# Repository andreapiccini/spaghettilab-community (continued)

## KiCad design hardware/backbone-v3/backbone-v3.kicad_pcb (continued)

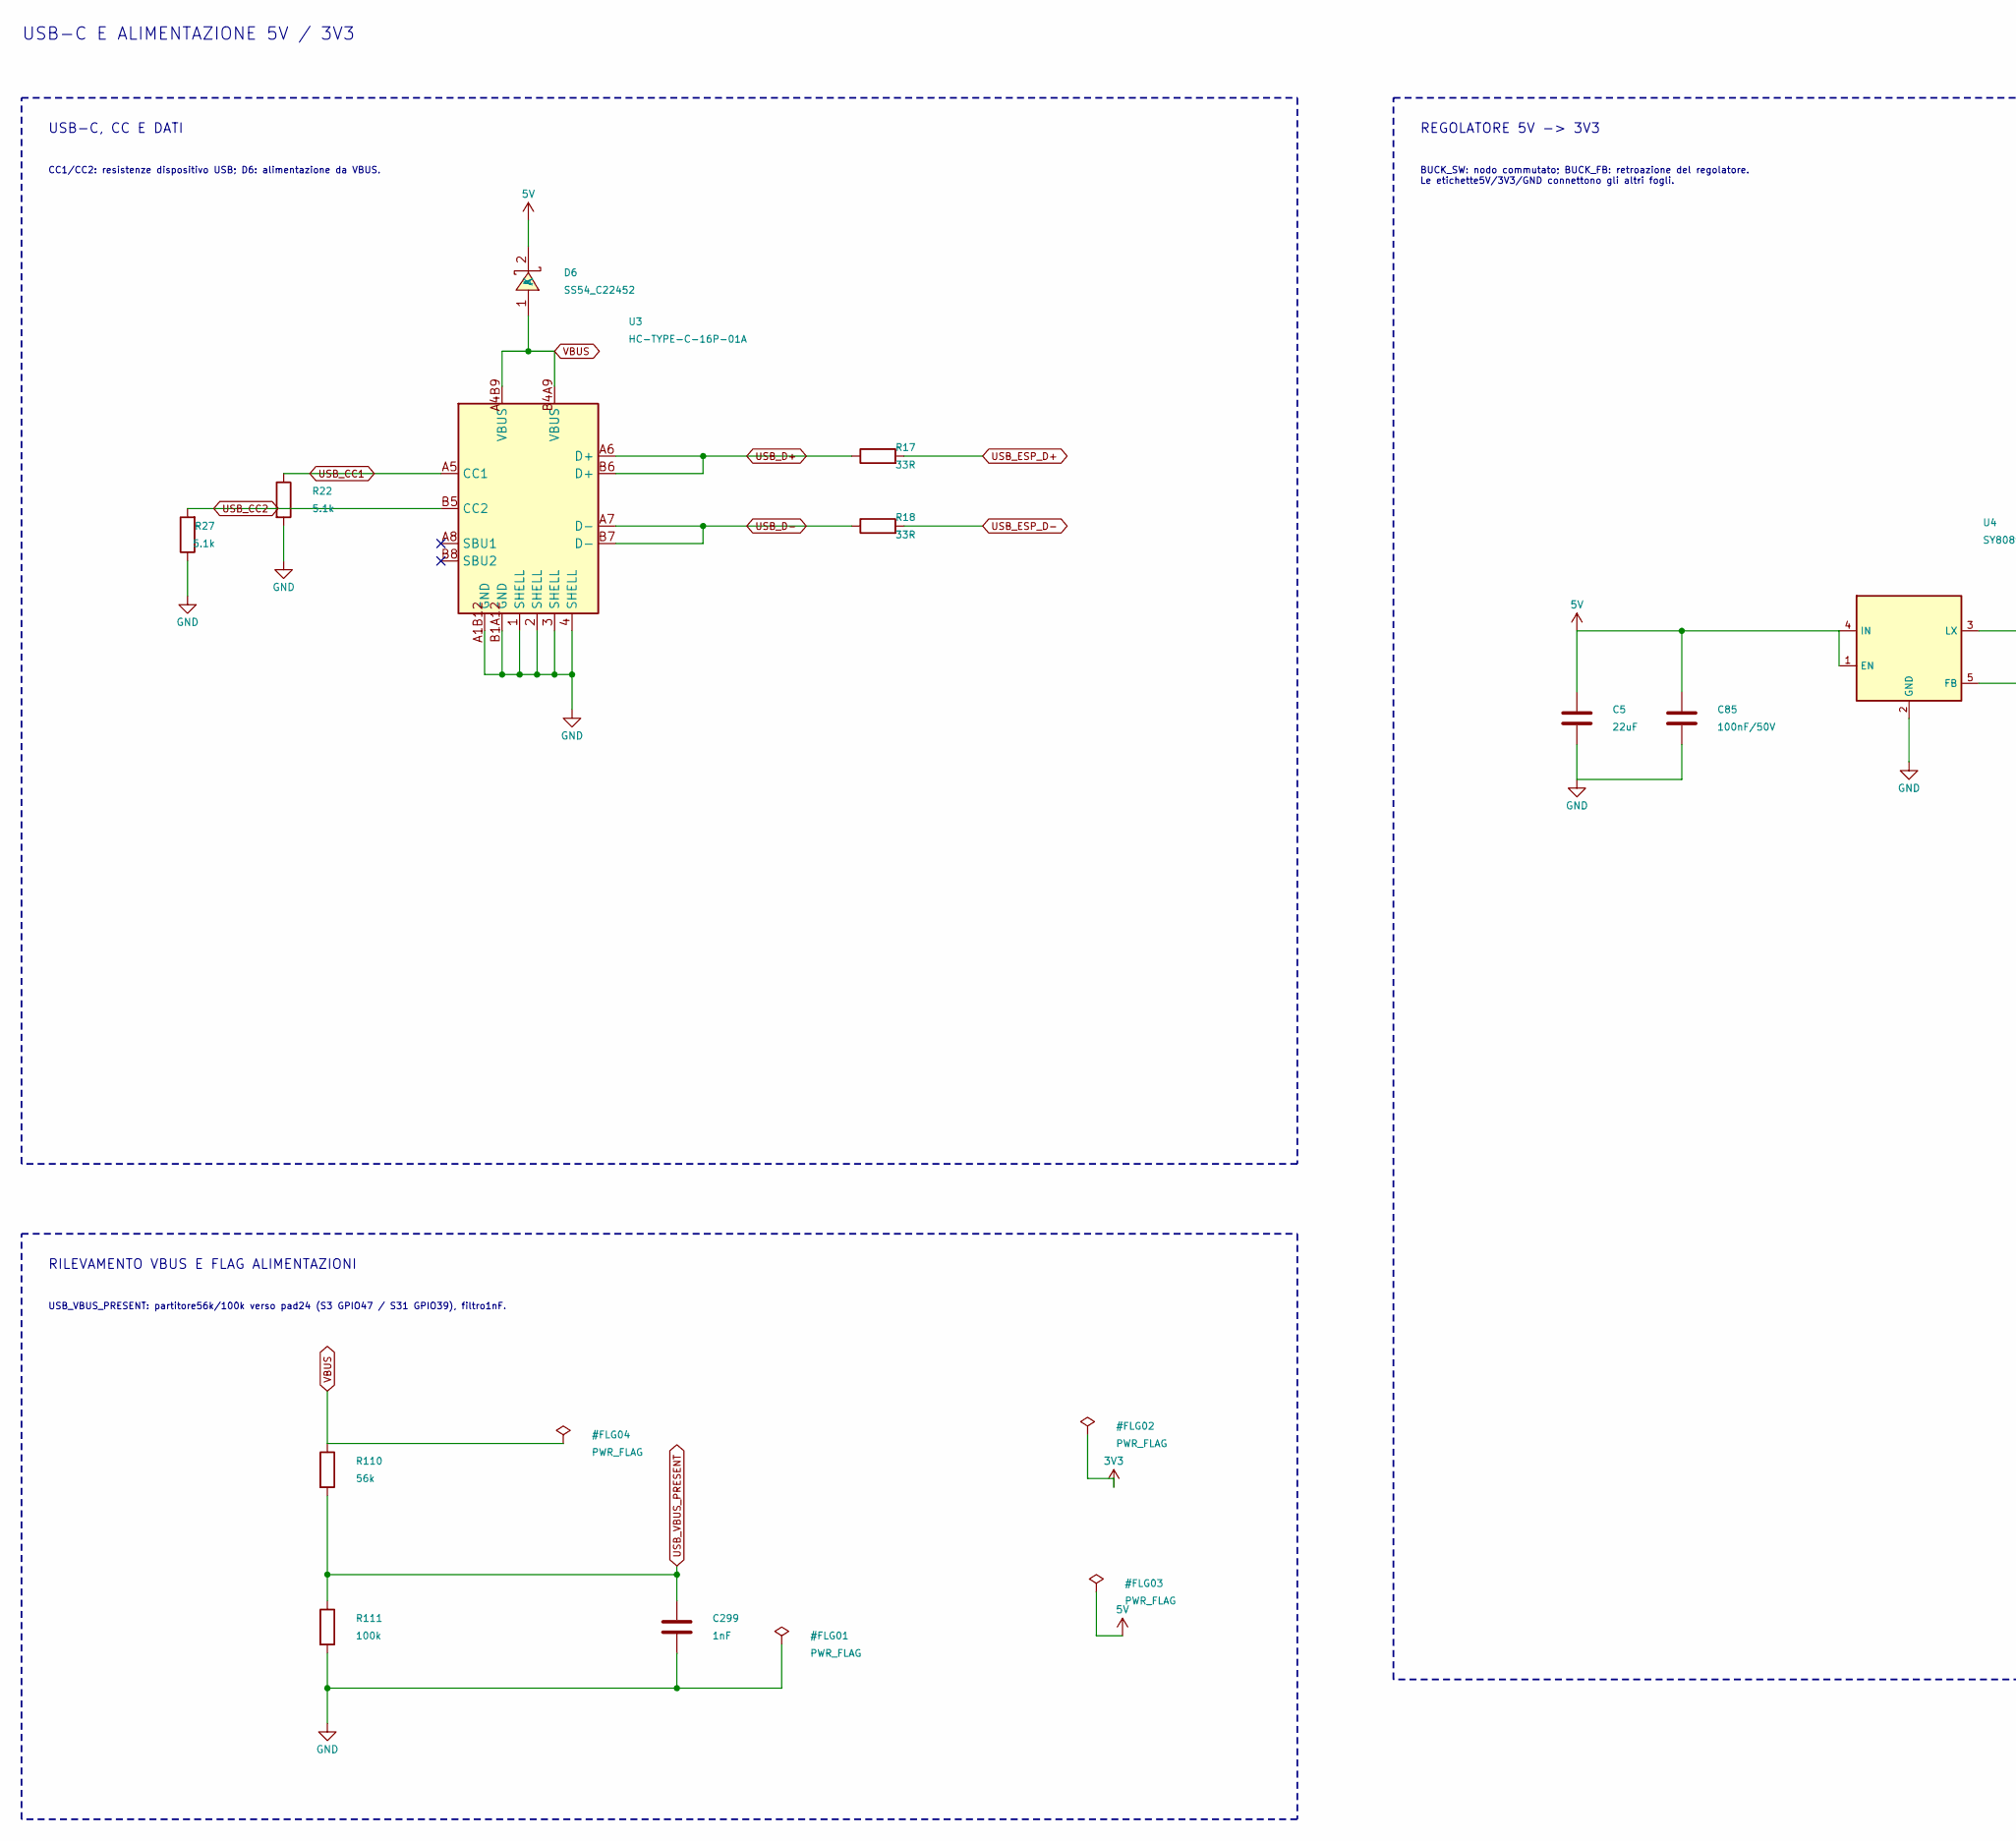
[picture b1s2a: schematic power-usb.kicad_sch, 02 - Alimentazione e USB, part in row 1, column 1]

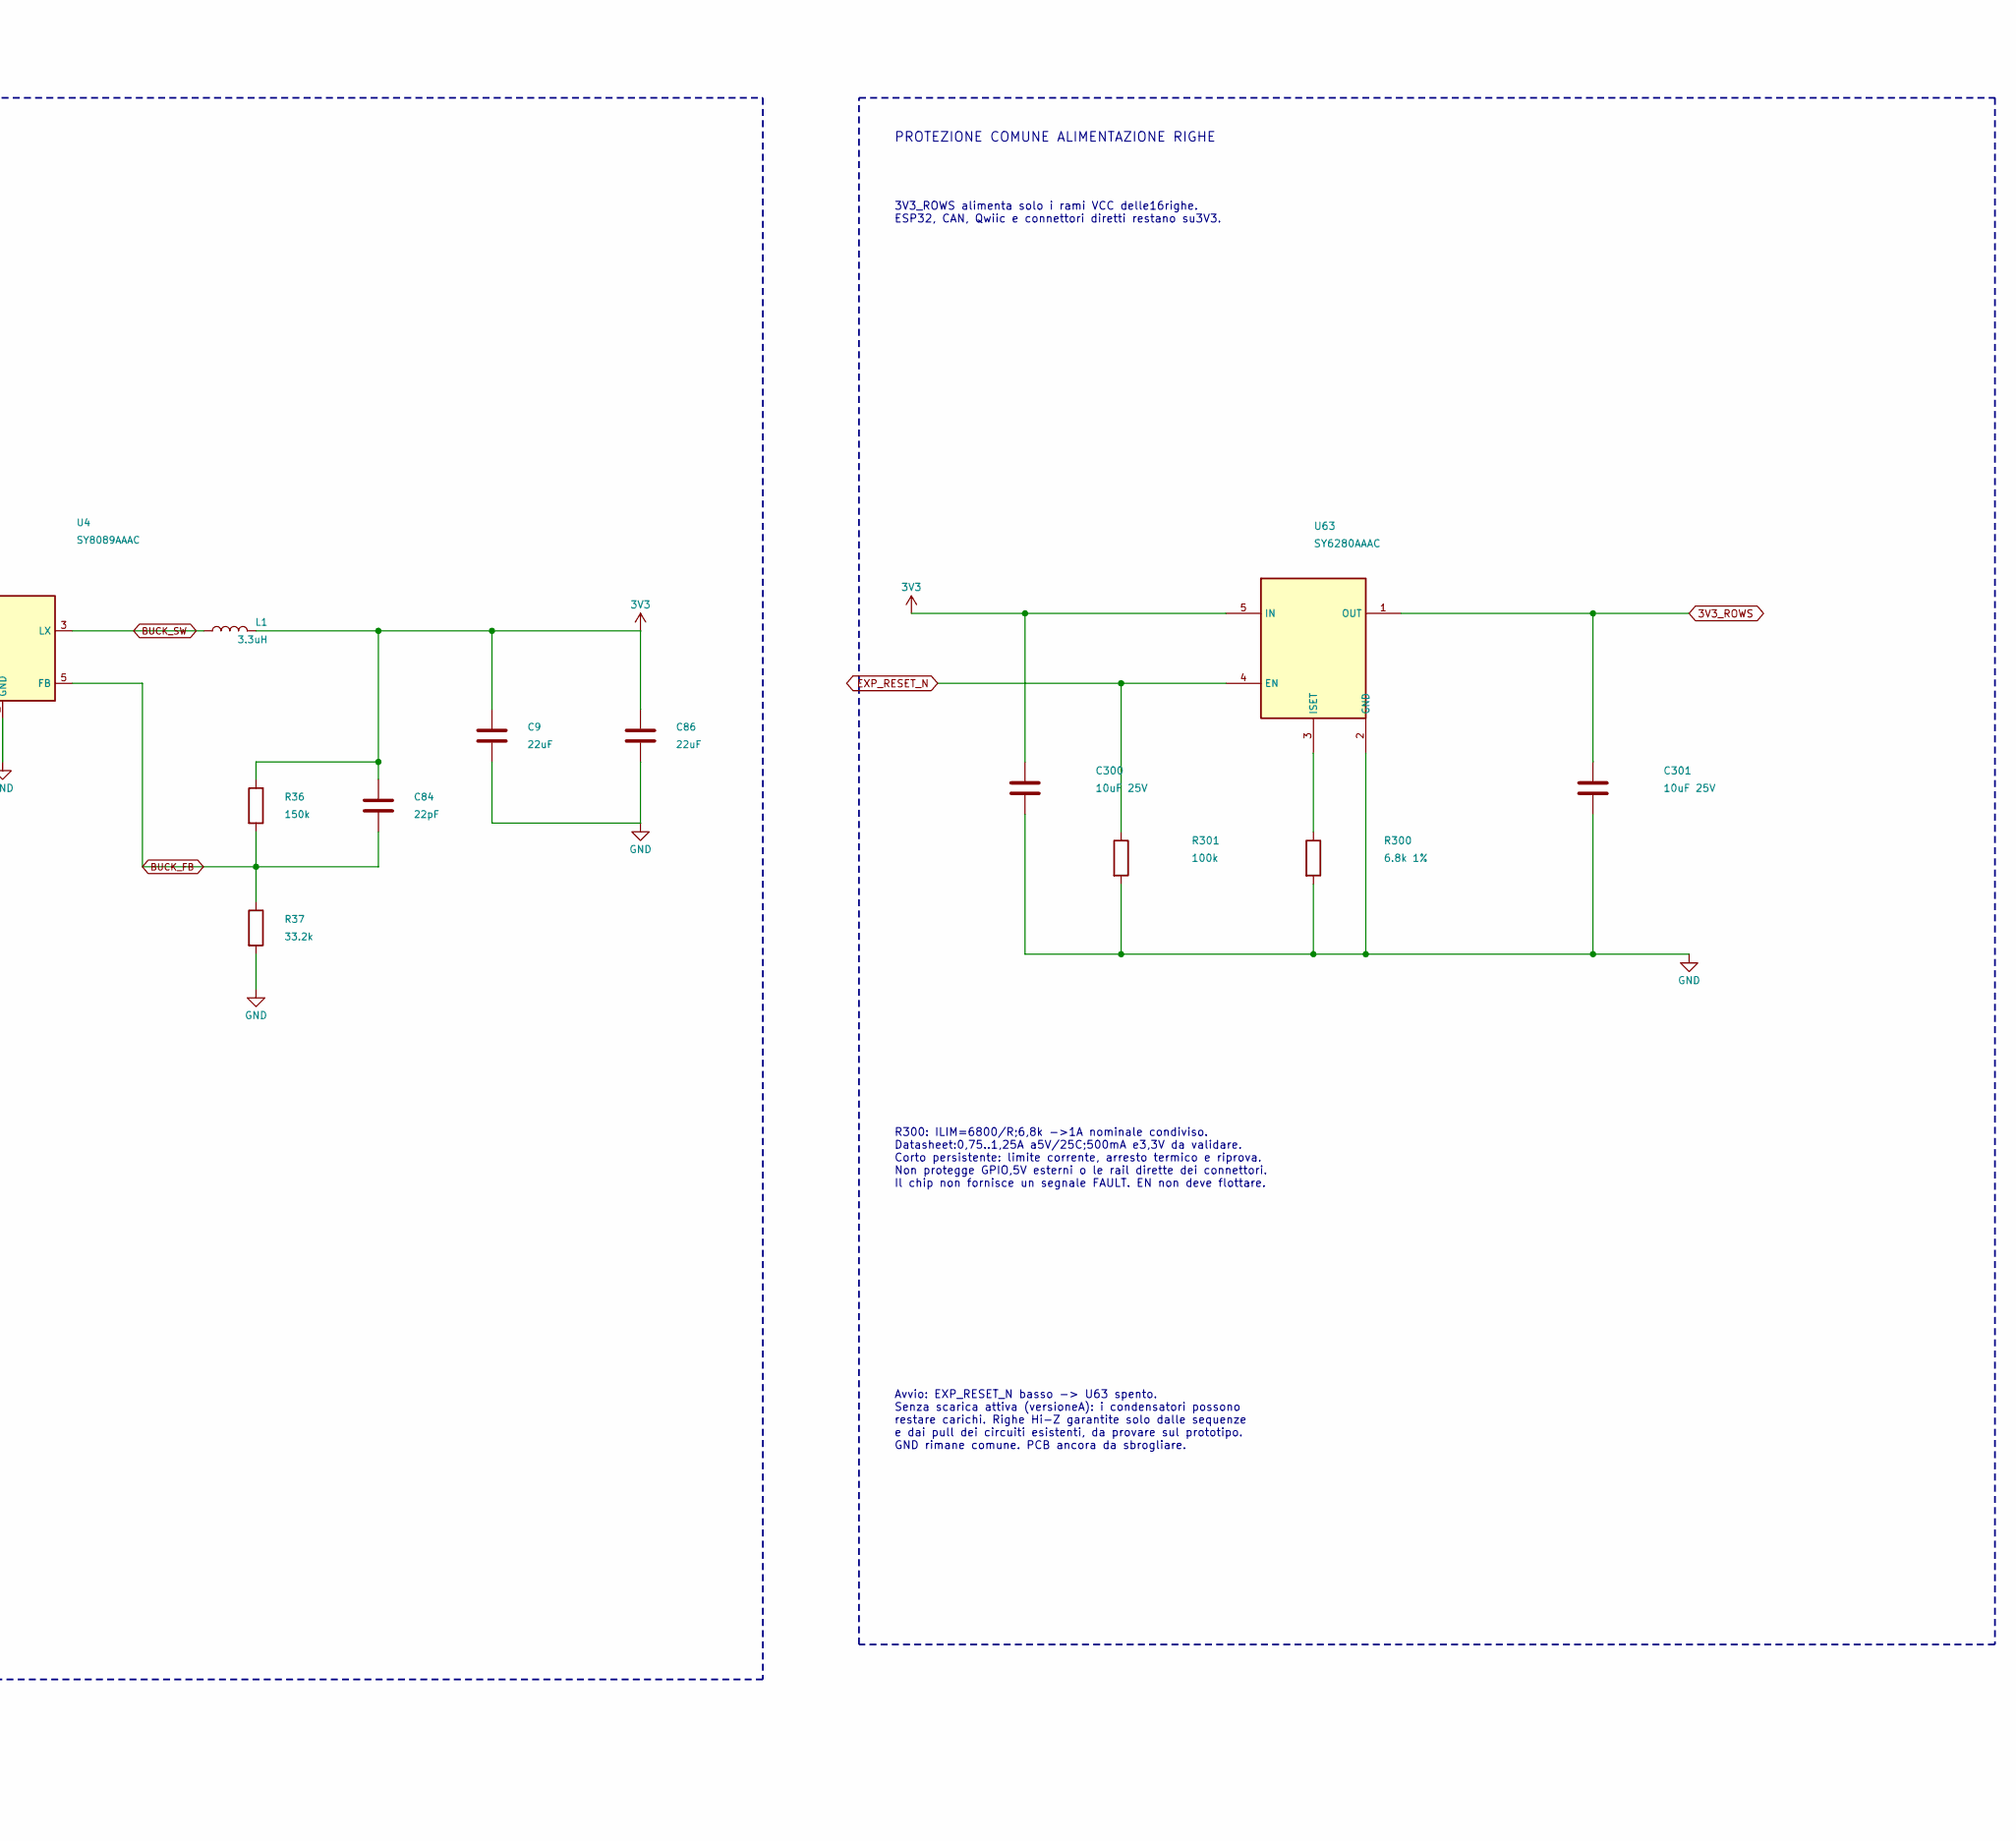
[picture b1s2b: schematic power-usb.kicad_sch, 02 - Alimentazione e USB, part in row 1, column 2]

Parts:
C5, C9, C86: 22uF; C_0603_1608Metric; MPN CL10A226MP8NUNE; LCSC Part C86295
C84: 22pF; C_0603_1608Metric; MPN CL10C220JB8NNNC; LCSC Part C1653
C85: 100nF/50V; C_0603_1608Metric; MPN CL10B104KB8NNNC; LCSC Part C1591
C299: 1nF; C_0603_1608Metric
C300, C301: 10uF 25V; C_0805_2012Metric; MPN CL21A106KAYNNNE; LCSC Part C15850
D6: SS54_C22452; SMA_L4.4-W2.8-LS5.4-R-RD; MPN SS54; LCSC Part C22452
L1: 3.3uH; L_XRTC404012S; MPN XRTC404012S3R3MBCA; LCSC Part C39846848
R17, R18: 33R; R0603; LCSC Part C2909394
R22, R27: 5.1k; R0603; LCSC Part C2907044
R36: 150k; R_0603_1608Metric; MPN 0603WAF1503T5E; LCSC Part C22807
R37: 33.2k; R_0603_1608Metric; MPN 0603WAF3322T5E; LCSC Part C23003
R110: 56k; R_0603_1608Metric
R111: 100k; R_0603_1608Metric
R300: 6.8k 1%; R_0603_1608Metric; MPN 0603WAF6801T5E; LCSC Part C23212
R301: 100k; R_0603_1608Metric; MPN 0603WAF1003T5E; LCSC Part C25803
U3: HC-TYPE-C-16P-01A; USB-C-SMD_HC-TYPE-C-16P-01A_ClearSilk; MPN HC-TYPE-C-16P-01A; LCSC Part C2894897
U4: SY8089AAAC; SOT-23-5; MPN SY8089AAAC; LCSC Part C78988
U63: SY6280AAAC; SOT-23-5; MPN SY6280AAAC; LCSC Part C207620

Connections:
3V3: C9.1, C84.1, C86.1, C300.1, L1.2, R36.1, U63.5 (IN); also elsewhere on the board
3V3_ROWS: C301.1, U63.1 (OUT); also elsewhere on the board
BUCK_FB: C84.2, R36.2, R37.1, U4.5 (FB)
BUCK_SW: L1.1, U4.3 (LX)
EXP_RESET_N: R301.1, U63.4 (EN); also elsewhere on the board
GND: C5.2, C9.2, C85.2, C86.2, C299.2, C300.2, C301.2, R22.2, R27.1, R37.2, R111.2, R300.2, R301.2, U3.1 (SHELL), U3.2 (SHELL), U3.3 (SHELL), U3.4 (SHELL), U3.A1B12 (GND), U3.B1A12 (GND), U4.2 (GND), U63.2 (GND); also elsewhere on the board
unnamed: R300.1, U63.3 (ISET)
USB_CC1: R22.1, U3.A5 (CC1)
USB_CC2: R27.2, U3.B5 (CC2)
USB_D+: R17.1, U3.A6 (D+), U3.B6 (D+)
USB_D-: R18.1, U3.A7 (D-), U3.B7 (D-)
USB_ESP_D+: R17.2; also elsewhere on the board
USB_ESP_D-: R18.2; also elsewhere on the board
USB_VBUS_PRESENT: C299.1, R110.2, R111.1; also elsewhere on the board
VBUS: D6.1 (A), R110.1, U3.A4B9 (VBUS), U3.B4A9 (VBUS)

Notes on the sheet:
BUCK_SW: nodo commutato; BUCK_FB: retroazione del regolatore. Le etichette5V/3V3/GND connettono gli altri fogli.
REGOLATORE 5V -> 3V3
USB_VBUS_PRESENT: partitore56k/100k verso pad24 (S3 GPIO47 / S31 GPIO39), filtro1nF.
PROTEZIONE COMUNE ALIMENTAZIONE RIGHE
Avvio: EXP_RESET_N basso -> U63 spento. Senza scarica attiva (versioneA): i condensatori possono restare carichi. Righe Hi-Z garantite solo dalle sequenze e dai pull dei circuiti esistenti, da provare sul prototipo. GND rimane comune. PCB ancora da sbrogliare.
USB-C, CC E DATI
USB-C E ALIMENTAZIONE 5V / 3V3
3V3_ROWS alimenta solo i rami VCC delle16righe. ESP32, CAN, Qwiic e connettori diretti restano su3V3.
RILEVAMENTO VBUS E FLAG ALIMENTAZIONI
CC1/CC2: resistenze dispositivo USB; D6: alimentazione da VBUS.
R300: ILIM=6800/R;6,8k ->1A nominale condiviso. Datasheet:0,75..1,25A a5V/25C;500mA e3,3V da validare. Corto persistente: limite corrente, arresto termico e riprova. Non protegge GPIO,5V esterni o le rail dirette dei connettori. Il chip non fornisce un segnale FAULT. EN non deve flottare.

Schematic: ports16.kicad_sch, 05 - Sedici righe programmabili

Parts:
C238, C239, C241, C242: 100nF; C_0603_1608Metric
J18, J19, J21, J22, J23, J24, J30, J31: HX PM2.54-1x8P TP-YQ; Hanxia_C42380985_1x08_Compact_Study; MPN HX PM2.54-1x8P TP-YQ; LCSC Part C42380985
Q30, Q31, Q32, Q33, Q34, Q35, Q36, Q37, Q44, Q45, Q46, Q47, Q48, Q49, Q50, Q51: AO3401A; SOT-23; MPN AO3401A; LCSC Part C15127
Q100, Q101, Q102, Q103, Q104, Q105, Q106, Q107, Q108, Q109, Q110, Q111, Q112, Q113, Q114, Q115: AO3400A; SOT-23; MPN AO3400A; LCSC Part C20917
RN1, RN2, RN3, RN4, RN5, RN6, RN7, RN8, RN9, RN10, RN11, RN12: 100k; YC164_4x0603_100k
U1: ESP32-S3-WROOM-1-N8R2; ESP32-S3-WROOM-1_FlexyPin_N8R2_TwoSideCourtyard; MPN ESP32-S3-WROOM-1-N8R2
U50, U51, U53, U54: 74CBTLV3125PW,118; TSSOP-14_L5.0-W4.4-P0.65-LS6.4-BL; MPN 74CBTLV3125PW,118; LCSC Part C456149

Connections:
3V3: C238.1, C239.1, C241.1, C242.1, RN9.1, RN9.2, RN9.3, RN9.4, RN10.1, RN10.2, RN10.3, RN10.4, RN11.1, RN11.2, RN11.3, RN11.4, RN12.1, RN12.2, RN12.3, RN12.4, U50.14 (VCC), U51.14 (VCC), U53.14 (VCC), U54.14 (VCC); also elsewhere on the board
3V3_ROWS: Q30.2 (S), Q31.2 (S), Q32.2 (S), Q33.2 (S), Q34.2 (S), Q35.2 (S), Q36.2 (S), Q37.2 (S), Q44.2 (S), Q45.2 (S), Q46.2 (S), Q47.2 (S), Q48.2 (S), Q49.2 (S), Q50.2 (S), Q51.2 (S), RN1.1, RN1.2, RN1.3, RN1.4, RN2.1, RN2.2, RN2.3, RN2.4, RN3.1, RN3.2, RN3.3, RN3.4, RN4.1, RN4.2, RN4.3, RN4.4; also elsewhere on the board
GND: C238.2, C239.2, C241.2, C242.2, Q100.2 (S), Q101.2 (S), Q102.2 (S), Q103.2 (S), Q104.2 (S), Q105.2 (S), Q106.2 (S), Q107.2 (S), Q108.2 (S), Q109.2 (S), Q110.2 (S), Q111.2 (S), Q112.2 (S), Q113.2 (S), Q114.2 (S), Q115.2 (S), RN5.5, RN5.6, RN5.7, RN5.8, RN6.5, RN6.6, RN6.7, RN6.8, RN7.5, RN7.6, RN7.7, RN7.8, RN8.5, RN8.6, RN8.7, RN8.8, U50.7 (GND), U51.7 (GND), U53.7 (GND), U54.7 (GND); also elsewhere on the board
GPIO1: U1.39 (IO1), U50.2 (A); also elsewhere on the board
GPIO2: U1.38 (IO2), U53.2 (A); also elsewhere on the board
GPIO3: U1.15 (IO3), U50.5 (A); also elsewhere on the board
GPIO4: U1.4 (IO4), U51.2 (A); also elsewhere on the board
GPIO6: U1.6 (IO6), U50.9 (A); also elsewhere on the board
GPIO7: U1.7 (IO7), U50.12 (A); also elsewhere on the board
GPIO8: U1.12 (IO8), U53.5 (A); also elsewhere on the board
GPIO9: U1.17 (IO9), U53.9 (A); also elsewhere on the board
GPIO10: U1.18 (IO10), U53.12 (A); also elsewhere on the board
GPIO35: U1.28 (IO35), U51.5 (A); also elsewhere on the board
GPIO36: U1.29 (IO36), U51.9 (A); also elsewhere on the board
GPIO37: U1.30 (IO37), U51.12 (A); also elsewhere on the board
GPIO38: U1.31 (IO38), U54.2 (A); also elsewhere on the board
GPIO39: U1.32 (IO39), U54.5 (A); also elsewhere on the board
GPIO40: U1.33 (IO40), U54.9 (A); also elsewhere on the board
GPIO41: U1.34 (IO41), U54.12 (A); also elsewhere on the board
ROW_L01: J18.1, J19.1, J21.1, J30.1, Q30.3 (D), Q100.3 (D), U50.3 (B); also elsewhere on the board
ROW_L01_ISO_N: RN9.5, U50.1 (OE_N); also elsewhere on the board
ROW_L01_NG: Q100.1 (G), RN5.1; also elsewhere on the board
ROW_L01_PG: Q30.1 (G), RN1.5; also elsewhere on the board
ROW_L02: J18.2, J19.2, J21.2, J30.2, Q31.3 (D), Q101.3 (D), U50.6 (B); also elsewhere on the board
ROW_L02_ISO_N: RN9.6, U50.4 (OE_N); also elsewhere on the board
ROW_L02_NG: Q101.1 (G), RN5.2; also elsewhere on the board
ROW_L02_PG: Q31.1 (G), RN1.6; also elsewhere on the board
ROW_L03: J18.3, J19.3, J21.3, J30.3, Q32.3 (D), Q102.3 (D), U50.8 (B); also elsewhere on the board
ROW_L03_ISO_N: RN9.7, U50.10 (OE_N); also elsewhere on the board
ROW_L03_NG: Q102.1 (G), RN5.3; also elsewhere on the board
ROW_L03_PG: Q32.1 (G), RN1.7; also elsewhere on the board
ROW_L04: J18.4, J19.4, J21.4, J30.4, Q33.3 (D), Q103.3 (D), U50.11 (B); also elsewhere on the board
ROW_L04_ISO_N: RN9.8, U50.13 (OE_N); also elsewhere on the board
ROW_L04_NG: Q103.1 (G), RN5.4; also elsewhere on the board
ROW_L04_PG: Q33.1 (G), RN1.8; also elsewhere on the board
ROW_L05: J18.5, J19.5, J21.5, J30.5, Q34.3 (D), Q104.3 (D), U51.3 (B); also elsewhere on the board
ROW_L05_ISO_N: RN10.5, U51.1 (OE_N); also elsewhere on the board
ROW_L05_NG: Q104.1 (G), RN6.1; also elsewhere on the board
ROW_L05_PG: Q34.1 (G), RN2.5; also elsewhere on the board
ROW_L06: J18.6, J19.6, J21.6, J30.6, Q35.3 (D), Q105.3 (D), U51.6 (B); also elsewhere on the board
ROW_L06_ISO_N: RN10.6, U51.4 (OE_N); also elsewhere on the board
ROW_L06_NG: Q105.1 (G), RN6.2; also elsewhere on the board
ROW_L06_PG: Q35.1 (G), RN2.6; also elsewhere on the board
ROW_L07: J18.7, J19.7, J21.7, J30.7, Q36.3 (D), Q106.3 (D), U51.8 (B); also elsewhere on the board
ROW_L07_ISO_N: RN10.7, U51.10 (OE_N); also elsewhere on the board
ROW_L07_NG: Q106.1 (G), RN6.3; also elsewhere on the board
ROW_L07_PG: Q36.1 (G), RN2.7; also elsewhere on the board
ROW_L08: J18.8, J19.8, J21.8, J30.8, Q37.3 (D), Q107.3 (D), U51.11 (B); also elsewhere on the board
ROW_L08_ISO_N: RN10.8, U51.13 (OE_N); also elsewhere on the board
ROW_L08_NG: Q107.1 (G), RN6.4; also elsewhere on the board
ROW_L08_PG: Q37.1 (G), RN2.8; also elsewhere on the board
ROW_R01: J22.1, J23.1, J24.1, J31.1, Q44.3 (D), Q108.3 (D), U53.3 (B); also elsewhere on the board
ROW_R01_ISO_N: RN11.5, U53.1 (OE_N); also elsewhere on the board
ROW_R01_NG: Q108.1 (G), RN7.1; also elsewhere on the board
ROW_R01_PG: Q44.1 (G), RN3.5; also elsewhere on the board
ROW_R02: J22.2, J23.2, J24.2, J31.2, Q45.3 (D), Q109.3 (D), U53.6 (B); also elsewhere on the board
ROW_R02_ISO_N: RN11.6, U53.4 (OE_N); also elsewhere on the board
ROW_R02_NG: Q109.1 (G), RN7.2; also elsewhere on the board
ROW_R02_PG: Q45.1 (G), RN3.6; also elsewhere on the board
ROW_R03: J22.3, J23.3, J24.3, J31.3, Q46.3 (D), Q110.3 (D), U53.8 (B); also elsewhere on the board
ROW_R03_ISO_N: RN11.7, U53.10 (OE_N); also elsewhere on the board
ROW_R03_NG: Q110.1 (G), RN7.3; also elsewhere on the board
ROW_R03_PG: Q46.1 (G), RN3.7; also elsewhere on the board
ROW_R04: J22.4, J23.4, J24.4, J31.4, Q47.3 (D), Q111.3 (D), U53.11 (B); also elsewhere on the board
ROW_R04_ISO_N: RN11.8, U53.13 (OE_N); also elsewhere on the board
ROW_R04_NG: Q111.1 (G), RN7.4; also elsewhere on the board
ROW_R04_PG: Q47.1 (G), RN3.8; also elsewhere on the board
ROW_R05: J22.5, J23.5, J24.5, J31.5, Q48.3 (D), Q112.3 (D), U54.3 (B); also elsewhere on the board
ROW_R05_ISO_N: RN12.5, U54.1 (OE_N); also elsewhere on the board
ROW_R05_NG: Q112.1 (G), RN8.1; also elsewhere on the board
ROW_R05_PG: Q48.1 (G), RN4.5; also elsewhere on the board
ROW_R06: J22.6, J23.6, J24.6, J31.6, Q49.3 (D), Q113.3 (D), U54.6 (B); also elsewhere on the board
ROW_R06_ISO_N: RN12.6, U54.4 (OE_N); also elsewhere on the board
ROW_R06_NG: Q113.1 (G), RN8.2; also elsewhere on the board
ROW_R06_PG: Q49.1 (G), RN4.6; also elsewhere on the board
ROW_R07: J22.7, J23.7, J24.7, J31.7, Q50.3 (D), Q114.3 (D), U54.8 (B); also elsewhere on the board
ROW_R07_ISO_N: RN12.7, U54.10 (OE_N); also elsewhere on the board
ROW_R07_NG: Q114.1 (G), RN8.3; also elsewhere on the board
ROW_R07_PG: Q50.1 (G), RN4.7; also elsewhere on the board
ROW_R08: J22.8, J23.8, J24.8, J31.8, Q51.3 (D), Q115.3 (D), U54.11 (B); also elsewhere on the board
ROW_R08_ISO_N: RN12.8, U54.13 (OE_N); also elsewhere on the board
ROW_R08_NG: Q115.1 (G), RN8.4; also elsewhere on the board
ROW_R08_PG: Q51.1 (G), RN4.8; also elsewhere on the board

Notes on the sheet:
A1 | pad 39 | ROW_L01
ADC DISTRIBUITI: A = 5 S3 / 4 S31; B = 4 S3 / 5 S31. Totale 9 / 9. U1A = servizi sul foglio principale; U1B..Q = contatti reali dello stesso socket. J18..J31: le unita A..H sono gli 8 contatti dello stesso connettore fisico. Percorso continuo per ogni riga: U1 -> isolatore -> 4 contatti Hanxia. Le 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
B5 | pad 31 | ROW_R05
DIG S3 / ADC S31
B2 | pad 12 | ROW_R02
ADC S3 / DIG S31
B6 | pad 32 | ROW_R06
A2 | pad 15 | ROW_L02
PG=0:VCC | NG=1:GND | ISO_N=0:GPIO
ADC S3 / ADC S31
16 RIGHE PROGRAMMABILI | VCC3V3 / GND / GPIO / HI-Z
B7 | pad 33 | ROW_R07
A6 | pad 28 | ROW_L06
B1 | pad 38 | ROW_R01
B4 | pad 18 | ROW_R04
B8 | pad 34 | ROW_R08
Ogni integrato ha4canali. UnitaE=alimentazione; bypass100nF.
A7 | pad 29 | ROW_L07
A4 | pad 7 | ROW_L04
ALIMENTAZIONE DEI4ISOLATORI
B3 | pad 17 | ROW_R03
A8 | pad 30 | ROW_L08
A3 | pad 6 | ROW_L03
A5 | pad 4 | ROW_L05
